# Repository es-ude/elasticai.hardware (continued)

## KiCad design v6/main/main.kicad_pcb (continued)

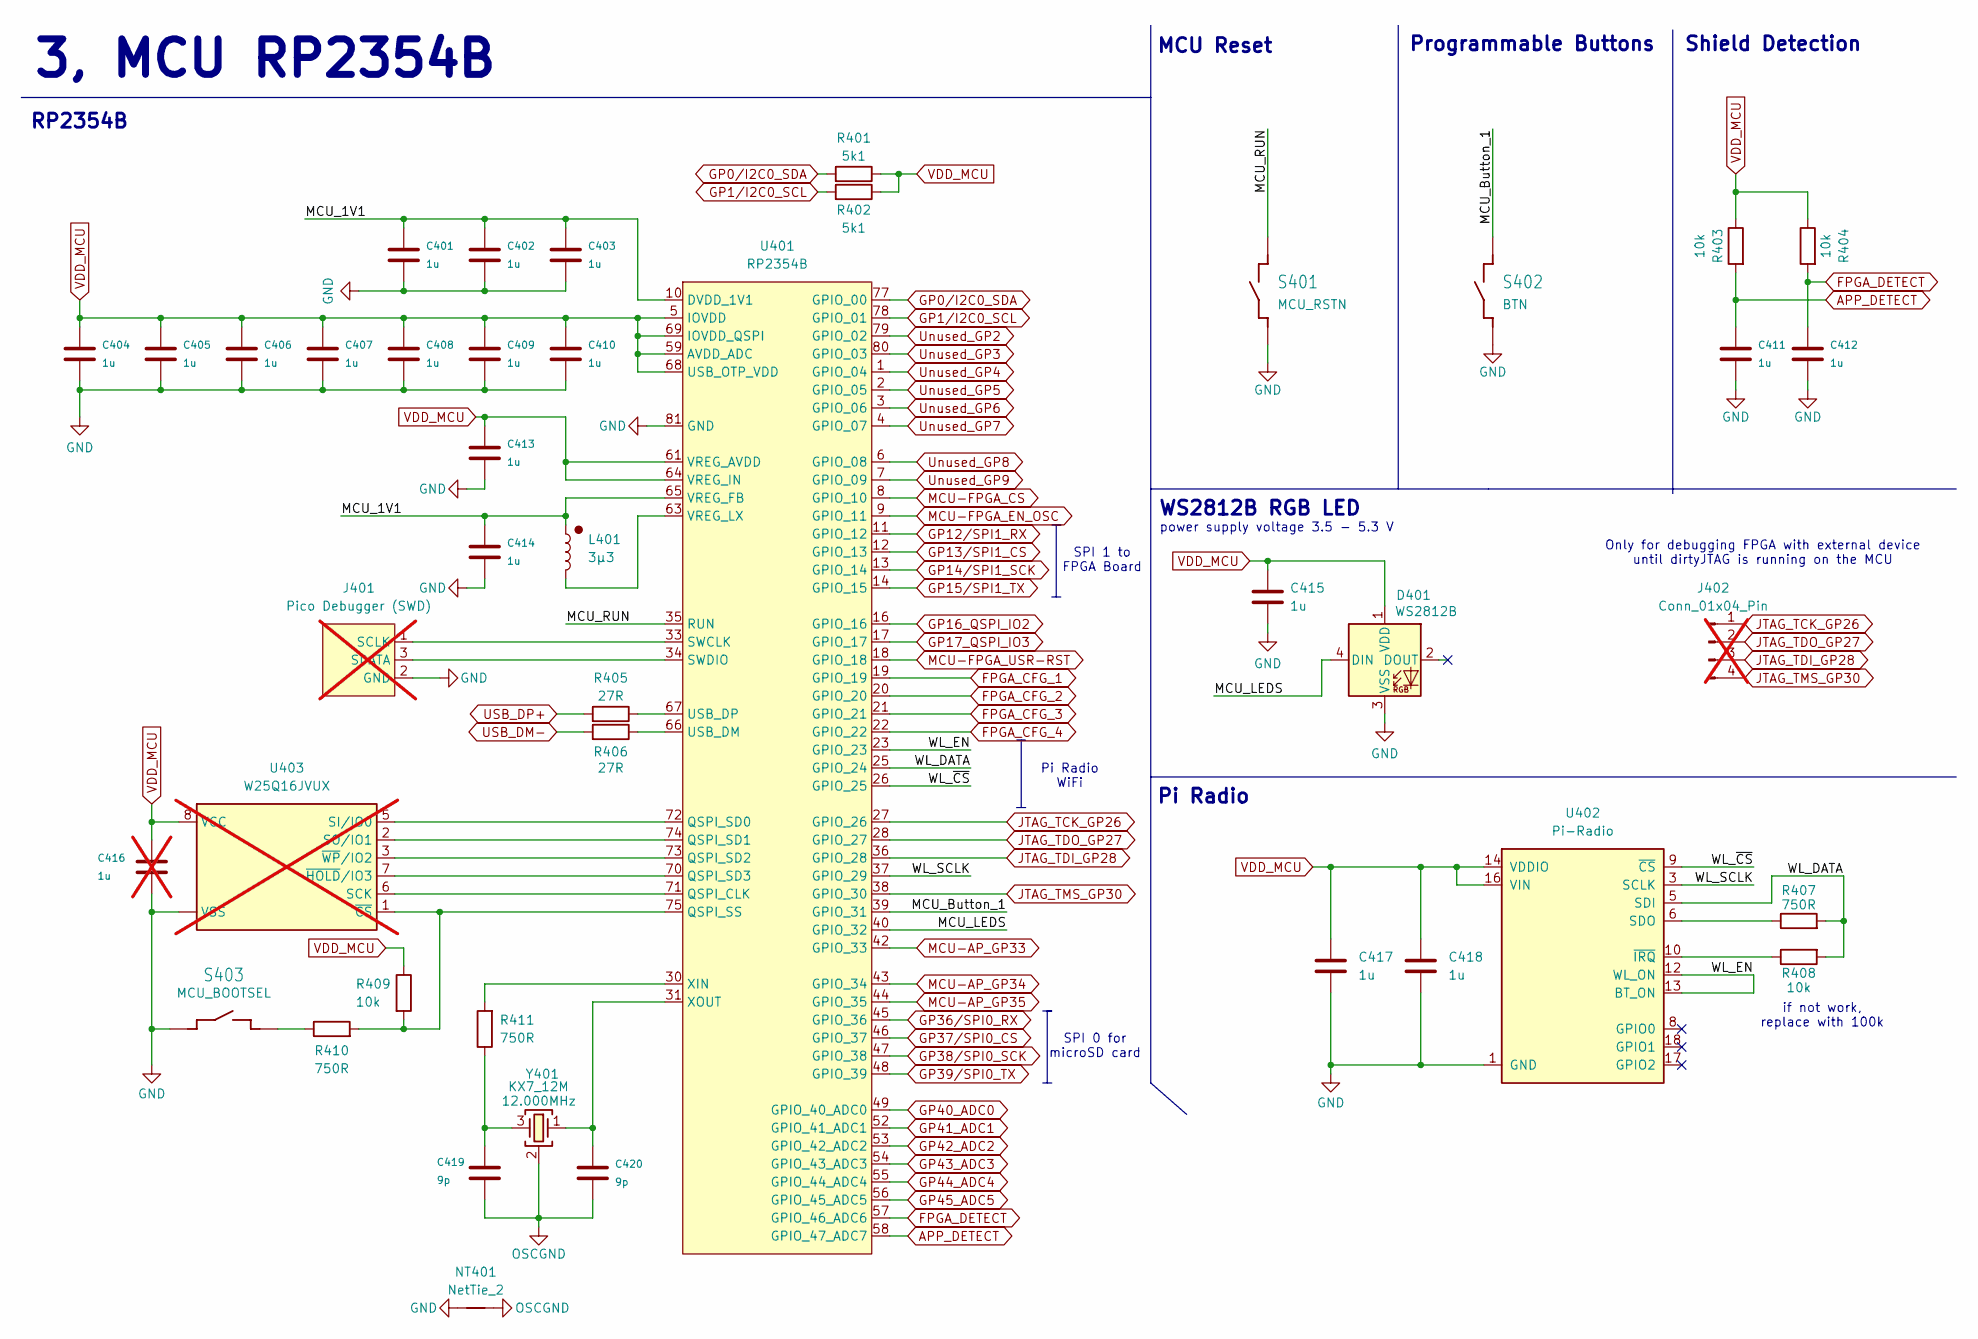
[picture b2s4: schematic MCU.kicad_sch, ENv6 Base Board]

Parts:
C401, C402, C403, C404, C405, C406, C407, C408, C409, C410, C411, C412, C413, C414, C415, C417, C418: 1u; C_0402_1005Metric
C416: 1u; C_0402_1005Metric; not fitted
C419, C420: 9p; C_0402_1005Metric
D401: WS2812B; LED_WS2812B_PLCC4_5.0x5.0mm_P3.2mm
J401: Pico Debugger (SWD); PinHeader_1x03_P2.00mm_Vertical; not fitted
J402: Conn_01x04_Pin; PinSocket_1x04_P2.00mm_Vertical; not fitted
L401: 3µ3; L_0805_2012_metric_Alligned_HandSolder; MPN AOTA-B201610S3R3-101-T
NT401: NetTie_2; NetTie-2_SMD_Pad0.5mm
R401, R402: 5k1; R_0402_1005Metric
R403, R404, R408, R409: 10k; R_0402_1005Metric
R405, R406: 27R; R_0402_1005Metric
R407, R410, R411: 750R; R_0402_1005Metric
S401: MCU_RSTN; TACTILE-SWITCH; MPN 612-TL3365AF180QG
S402: BTN; TACTILE-SWITCH; MPN 612-TL3365AF180QG
S403: MCU_BOOTSEL; TACTILE-SWITCH; MPN 612-TL3365AF180QG
U401: RP2354B; QFN-80_EP_10x10_Pitch0.4mm
U402: Pi-Radio; RPi-Radio-Module
U403: W25Q16JVUX; USON-8-1EP_3x2mm_P0.5mm_EP0.2x1.6mm; not fitted
Y401: KX7_12M; KX-7; MPN ABM8G-25.000MHZ-18-D2Y-T3

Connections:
/MCU/MCU_1V1: C401.2, C402.2, C403.2, C414.2, L401.1, U401.10 (DVDD_1V1), U401.32 (DVDD_1V1), U401.51 (DVDD_1V1), U401.65 (VREG_FB)
/MCU/MCU_Button_1: S402.3 (2), S402.4 (2), U401.39 (GPIO_31)
/MCU/MCU_LEDS: D401.4 (DIN), U401.40 (GPIO_32)
/MCU/MCU_RUN: S401.3 (2), S401.4 (2), U401.35 (RUN)
/MCU/WL_DATA: R407.2, R408.2, U401.25 (GPIO_24), U402.5 (SDI)
/MCU/WL_EN: U401.23 (GPIO_23), U402.12 (WL_ON), U402.13 (BT_ON)
/MCU/WL_SCLK: U401.37 (GPIO_29), U402.3 (SCLK)
/MCU/WL_~CS: U401.26 (GPIO_25), U402.9 (~CS)
APP_DETECT: C411.2, R403.2, U401.58 (GPIO_47_ADC7); also elsewhere on the board
FPGA_CFG_1: U401.19 (GPIO_19); also elsewhere on the board
FPGA_CFG_2: U401.20 (GPIO_20); also elsewhere on the board
FPGA_CFG_3: U401.21 (GPIO_21); also elsewhere on the board
FPGA_CFG_4: U401.22 (GPIO_22); also elsewhere on the board
FPGA_DETECT: C412.2, R404.2, U401.57 (GPIO_46_ADC6); also elsewhere on the board
GND: C401.1, C402.1, C403.1, C404.1, C405.1, C406.1, C407.1, C408.1, C409.1, C410.1, C411.1, C412.1, C413.1, C414.1, C415.2, C416.2, C417.2, C418.2, D401.3 (VSS), J401.2 (GND), NT401.1, S401.1, S401.2 (1), S402.1, S402.2 (1), S403.1, S403.2 (1), U401.62 (GND), U401.81 (GND), U402.1 (GND), U402.4 (GND), U402.7 (GND), U402.11 (GND), U402.15 (GND), U402.21 (GND), U403.4 (VSS), U403.9 (VSS); also elsewhere on the board
GP0/I2C0_SDA: R401.2, U401.77 (GPIO_00); also elsewhere on the board
GP1/I2C0_SCL: R402.2, U401.78 (GPIO_01); also elsewhere on the board
GP12/SPI1_RX: U401.11 (GPIO_12); also elsewhere on the board
GP13/SPI1_CS: U401.12 (GPIO_13); also elsewhere on the board
GP14/SPI1_SCK: U401.13 (GPIO_14); also elsewhere on the board
GP15/SPI1_TX: U401.14 (GPIO_15); also elsewhere on the board
GP16_QSPI_IO2: U401.16 (GPIO_16); also elsewhere on the board
GP17_QSPI_IO3: U401.17 (GPIO_17); also elsewhere on the board
GP36/SPI0_RX: U401.45 (GPIO_36); also elsewhere on the board
GP37/SPI0_CS: U401.46 (GPIO_37); also elsewhere on the board
GP38/SPI0_SCK: U401.47 (GPIO_38); also elsewhere on the board
GP39/SPI0_TX: U401.48 (GPIO_39); also elsewhere on the board
GP40_ADC0: U401.49 (GPIO_40_ADC0); also elsewhere on the board
GP41_ADC1: U401.52 (GPIO_41_ADC1); also elsewhere on the board
GP42_ADC2: U401.53 (GPIO_42_ADC2); also elsewhere on the board
GP43_ADC3: U401.54 (GPIO_43_ADC3); also elsewhere on the board
GP44_ADC4: U401.55 (GPIO_44_ADC4); also elsewhere on the board
GP45_ADC5: U401.56 (GPIO_45_ADC5); also elsewhere on the board
JTAG_TCK_GP26: J402.1, U401.27 (GPIO_26); also elsewhere on the board
JTAG_TDI_GP28: J402.3, U401.36 (GPIO_28); also elsewhere on the board
JTAG_TDO_GP27: J402.2, U401.28 (GPIO_27); also elsewhere on the board
JTAG_TMS_GP30: J402.4, U401.38 (GPIO_30); also elsewhere on the board
MCU-AP_GP33: U401.42 (GPIO_33); also elsewhere on the board
MCU-AP_GP34: U401.43 (GPIO_34); also elsewhere on the board
MCU-AP_GP35: U401.44 (GPIO_35); also elsewhere on the board
MCU-FPGA_CS: U401.8 (GPIO_10); also elsewhere on the board
MCU-FPGA_EN_OSC: U401.9 (GPIO_11); also elsewhere on the board
MCU-FPGA_USR-RST: U401.18 (GPIO_18); also elsewhere on the board
unnamed: C419.2, R411.1, Y401.3
unnamed: J401.1 (SCLK), U401.33 (SWCLK)
unnamed: J401.3 (SDATA), U401.34 (SWDIO)
unnamed: R410.1, S403.3 (2), S403.4 (2)
unnamed: U401.71 (QSPI_CLK), U403.6 (SCK)
unnamed: U401.72 (QSPI_SD0), U403.5 (SI/IO0)
unnamed: U401.74 (QSPI_SD1), U403.2 (SO/IO1)
unnamed: U401.73 (QSPI_SD2), U403.3 (~WP/IO2)
unnamed: U401.70 (QSPI_SD3), U403.7 (~HOLD/IO3)
unnamed: R409.2, R410.2, U401.75 (QSPI_SS), U403.1 (~CS)
unnamed: R406.1, U401.66 (USB_DM)
unnamed: R405.1, U401.67 (USB_DP)
unnamed: L401.2, U401.63 (VREG_LX)
unnamed: R411.2, U401.30 (XIN)
unnamed: C420.2, U401.31 (XOUT), Y401.1
unnamed: R407.1, U402.6 (SDO)
unnamed: R408.1, U402.10 (~IRQ)
OSCGND: C419.1, C420.1, NT401.2, Y401.2 (SH), Y401.4 (SH)
USB_DM-: R406.2; also elsewhere on the board
USB_DP+: R405.2; also elsewhere on the board
Unused_GP2: U401.79 (GPIO_02); also elsewhere on the board
Unused_GP3: U401.80 (GPIO_03); also elsewhere on the board
Unused_GP4: U401.1 (GPIO_04); also elsewhere on the board
Unused_GP5: U401.2 (GPIO_05); also elsewhere on the board
Unused_GP6: U401.3 (GPIO_06); also elsewhere on the board
Unused_GP7: U401.4 (GPIO_07); also elsewhere on the board
Unused_GP8: U401.6 (GPIO_08); also elsewhere on the board
Unused_GP9: U401.7 (GPIO_09); also elsewhere on the board
VDD_MCU: C404.2, C405.2, C406.2, C407.2, C408.2, C409.2, C410.2, C413.2, C415.1, C416.1, C417.1, C418.1, D401.1 (VDD), R401.1, R402.1, R403.1, R404.1, R409.1, U401.5 (IOVDD), U401.15 (IOVDD), U401.24 (IOVDD), U401.29 (IOVDD), U401.41 (IOVDD), U401.50 (IOVDD), U401.59 (AVDD_ADC), U401.60 (IOVDD), U401.61 (VREG_AVDD), U401.64 (VREG_IN), U401.68 (USB_OTP_VDD), U401.69 (IOVDD_QSPI), U401.76 (IOVDD), U402.14 (VDDIO), U402.16 (VIN), U403.8 (VCC); also elsewhere on the board

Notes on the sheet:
SPI 0 for microSD card
Programmable Buttons
Pi Radio WiFi
Only for debugging FPGA with external device until dirtyJTAG is running on the MCU
Pi Radio
if not work, replace with 100k
RP2354B
SPI 1 to FPGA Board
3, MCU RP2354B
power supply voltage 3.5 - 5.3 V
WS2812B RGB LED
Shield Detection
MCU Reset

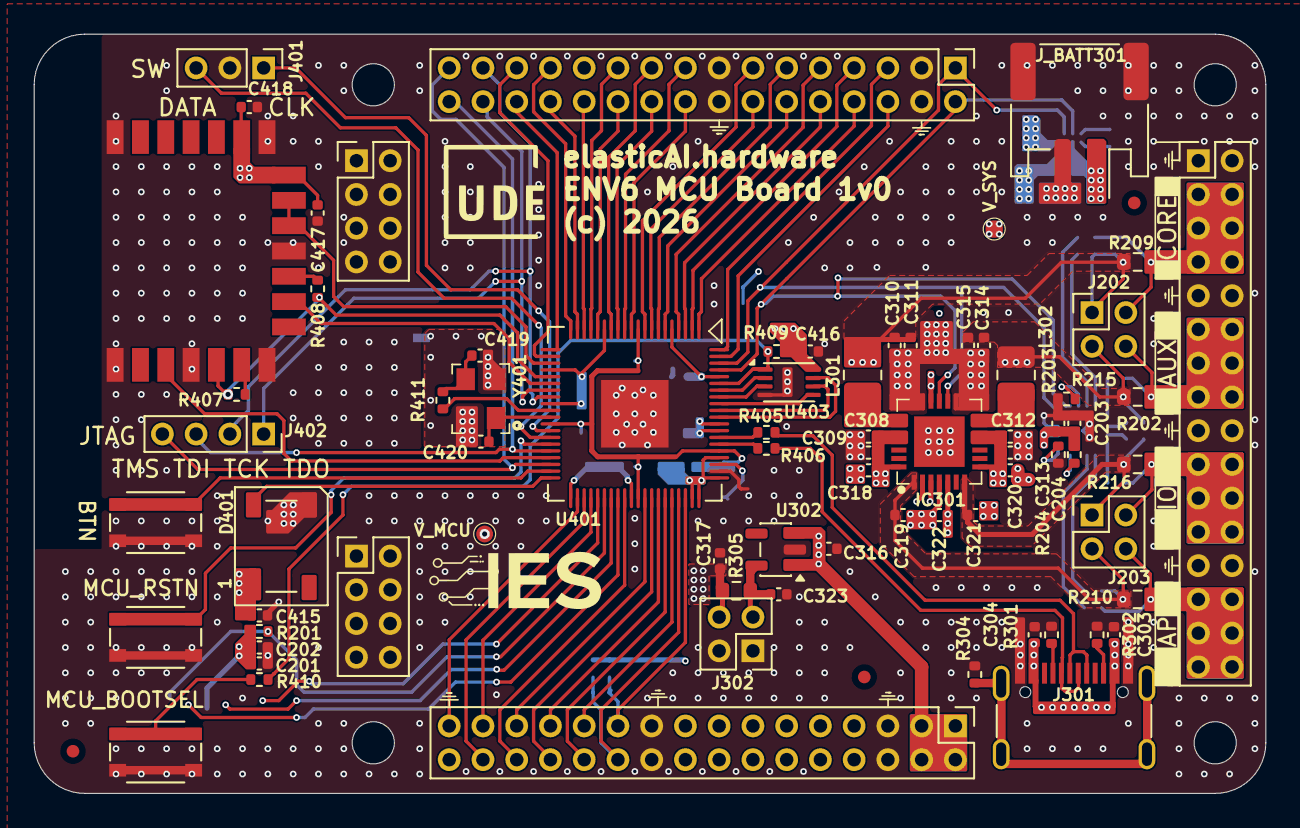
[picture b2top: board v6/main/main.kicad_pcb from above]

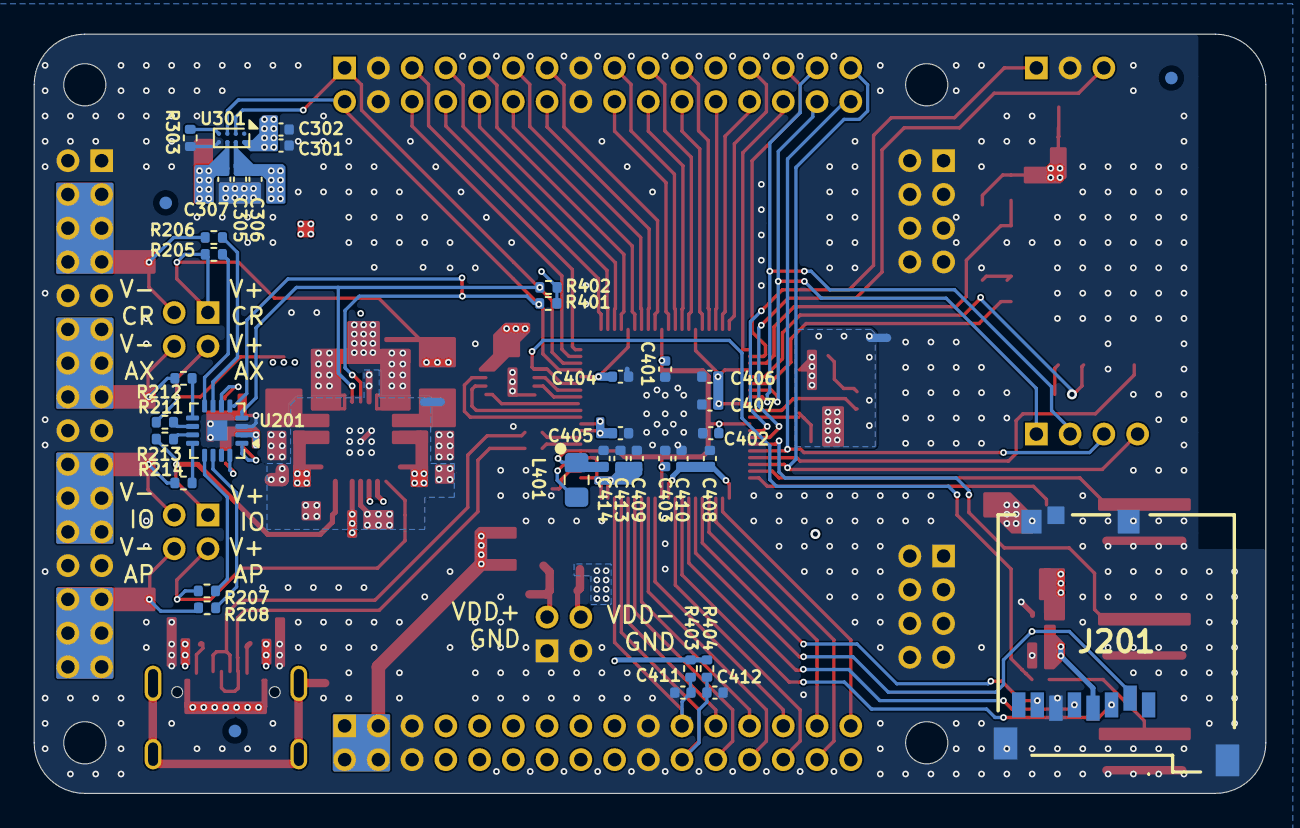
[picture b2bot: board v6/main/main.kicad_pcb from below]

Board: 4 copper layers, 73.0 x 45.0 mm, 113 parts (41 on the bottom side), 102 nets.

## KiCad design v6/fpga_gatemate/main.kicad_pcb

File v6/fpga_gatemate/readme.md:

# ENv6 FPGA Board: CologneChip GateMate M1A1/2

FPGA board (shield, rev 1.0) for the ENv6 base board with the CologneChip GateMate CCGM1A1 (schematic of the M1A1; the M1A2 is not designed yet). FPGA board ID: **2** (R1 + R2 + R3 = 750 Ω + 750 Ω + 27 Ω ≈ 1.5 kΩ to GND on `FPGA_DETECT`, see the [auto-identification](../readme.md#auto-identification-of-connected-boards)).

## Contents (KiCad sheets)

| Sheet         | Content                                                                                                          |
|---------------|------------------------------------------------------------------------------------------------------------------|
| `fpga_config` | IS25LP064D quad-SPI flash (U8), configuration mode pins `CFG_MD0 … 3`, pull-ups, SerDes header (J1, not fitted)  |
| `fpga_power`  | Supply decoupling, Si5351A clock generator (U7) with 25 MHz crystal (Y1), test points TP1/TP2                    |
| `fpga_io`     | IO banks of the FPGA, status LED (D1 with R4 = 750 Ω)                                                            |
| `translation` | Five TXB0108 level shifters (U1 … U5) between the FPGA (`VDD_IO`) and the connector (`VDDD_MCU`)                 |
| `connectors`  | ENv6 connector (base board and application board), ID resistors R1 … R3                                          |

### Configuration and clock

- **Mode pins:** `CFG_MD0 … 3` have 10 kΩ pull-downs fitted (R15 … R18); the pull-ups to `VDD_IO` (R11 … R14) are not fitted. The default setting is therefore `0000`. A different mode is selected by fitting a pull-up and removing the pull-down.
- **Flash:** The IS25LP064D (U8) is connected to the SPI configuration pins of the FPGA and, via level shifter U3, to the SPI1/QSPI lines of the MCU. Pull-ups (R20 … R24, 10 kΩ to `VDD_IO`) are on `CFG_DONE`, `CFG_FAILED_N`, flash CS and the flash IO2/IO3 lines.
- **Clock:** The Si5351A (U7) is controlled via I2C directly from the connector (A1, A2) and enabled via `EN_FPGA_OSC` (A13). `CLK0` drives the FPGA clock input `CLK0` (`FPGA_SYS_CLK`, test point TP1) through a 27 Ω series resistor; `CLK7` is available at test point TP2. Spread spectrum is disabled (`SSEN` pulled low by R10, R9 not fitted). The crystal load capacitors C41 and C45 (12 pF) are placed but not fitted; the internal load capacitance of the Si5351A is used.
- **SerDes:** The SerDes lines (`SER_CLK`, `SER_TX`, `SER_RX`) are only routed to the pin header J1, which is not fitted. R19 (750 Ω) is the SerDes termination resistor.

## Power Supply

| Rail   | Pins      | Net label | Use                                                                                             |
|--------|-----------|-----------|-------------------------------------------------------------------------------------------------|
| `PSU1` | C3 … C8   | `1V0`     | FPGA core, PLL and SerDes (`VDD_CORE`)                                                          |
| `PSU2` | C11 … C16 | `2V5`     | All IO banks (`VDD_IO`), flash, `VCCA` of the level shifters, Si5351A output supplies, pull-ups |

`VDD_PLL` (R27), `VDD_SER_PLL` (R26) and `VDD_SER` (R25) are fed from `1V0` through a 27 Ω series resistor each. On the FPGA side each of these three nodes has 3 × 1 µF, 10 µF and 100 nF to GND as an RC filter. Replace the resistors by 0 Ω if the voltage drop at the pins gets too large (the datasheet allows 0.95 … 1.05 V in economy mode).

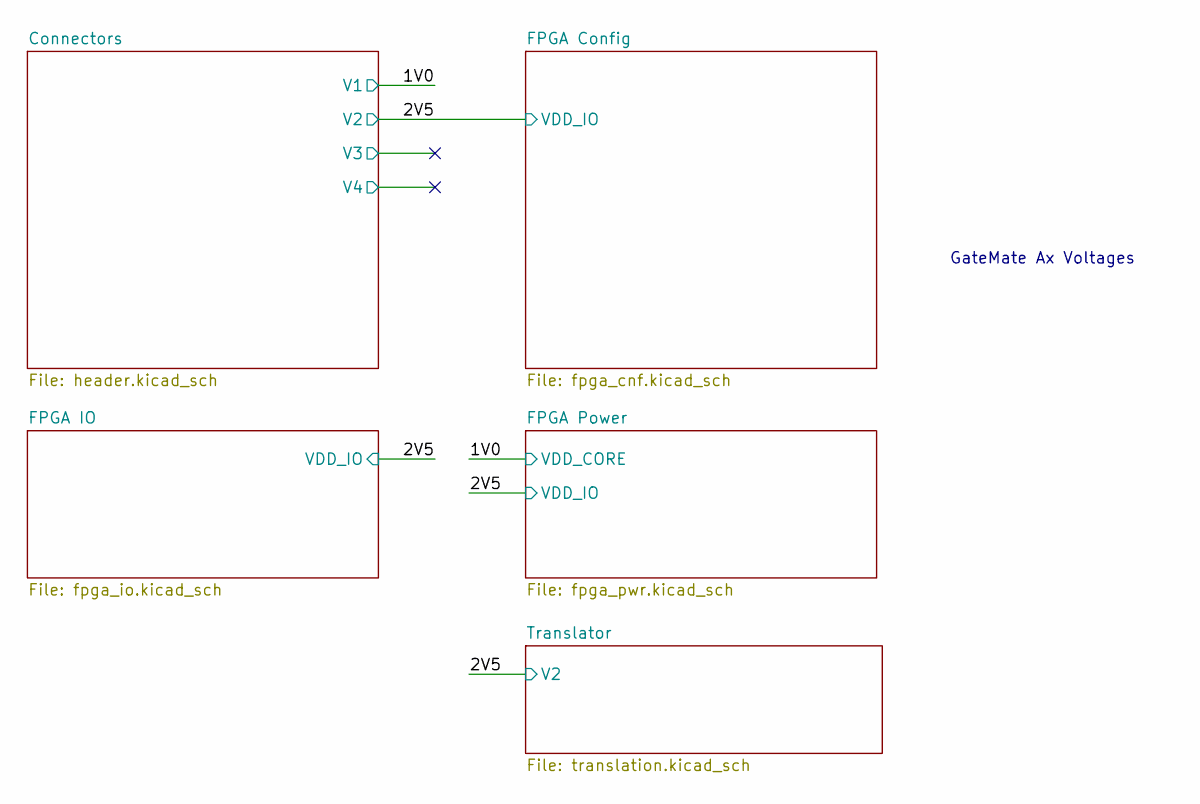
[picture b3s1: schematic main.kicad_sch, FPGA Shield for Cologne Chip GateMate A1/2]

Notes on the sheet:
GateMate Ax Voltages

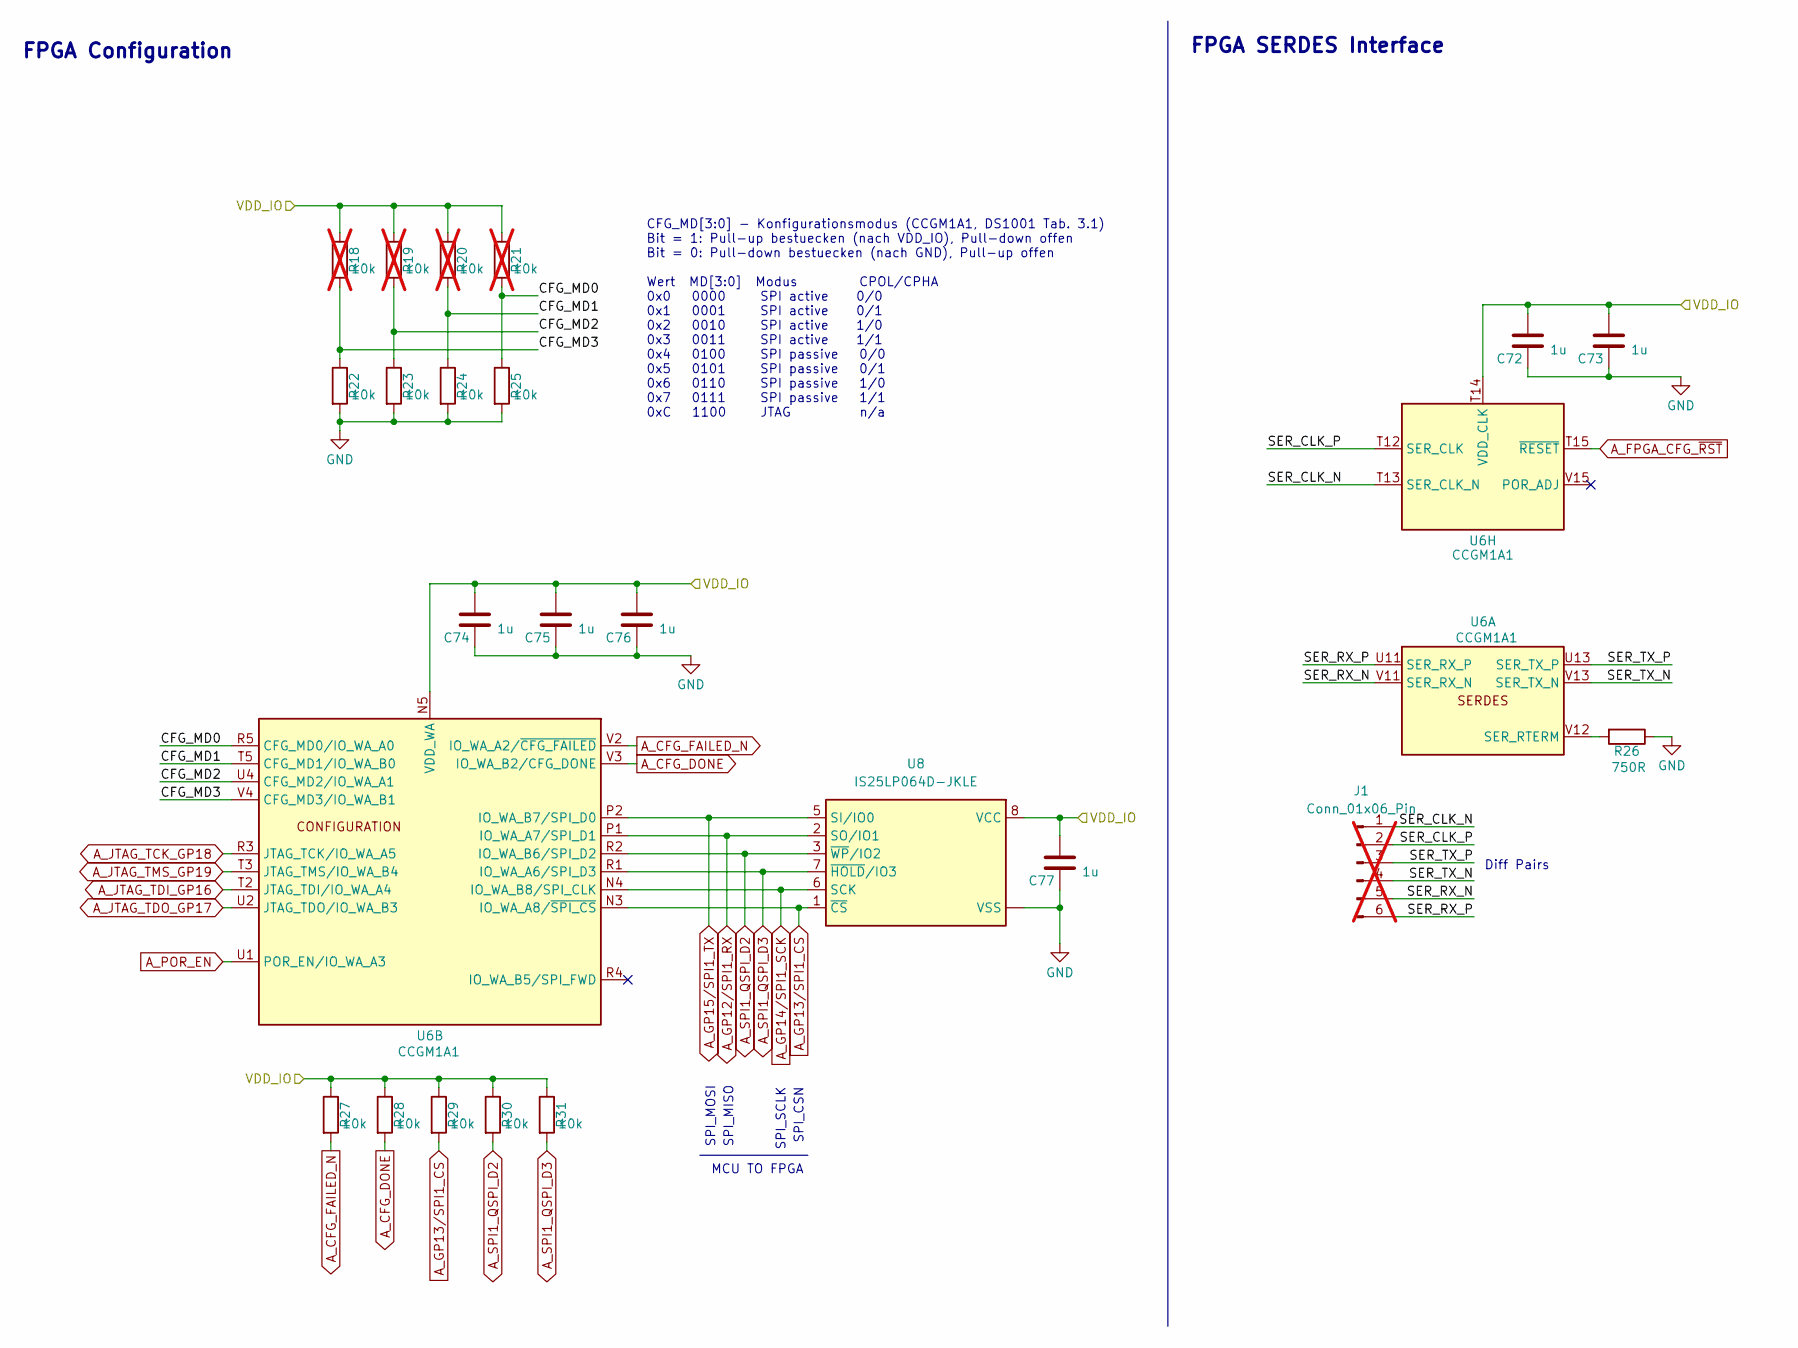
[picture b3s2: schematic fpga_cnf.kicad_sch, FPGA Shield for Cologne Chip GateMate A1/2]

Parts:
C72, C73, C74, C75, C76, C77: 1u; C_0402_1005Metric
J1: Conn_01x06_Pin; PinHeader_1x06_P2.54mm_Vertical; not fitted
R18, R19, R20, R21: 10k; R_0402_1005Metric; not fitted
R22, R23, R24, R25, R27, R28, R29, R30, R31: 10k; R_0402_1005Metric
R26: 750R; R_0402_1005Metric
U6: CCGM1A1; BGA-324_15.0x15.0mm_Layout18x18_P0.8mm_Ball0.5mm_Pad0.4mm_N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
U8: IS25LP064D-JKLE; WSON-8-1EP_6x5mm_P1.27mm_EP3.4x4.3mm

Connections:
/2V5: C72.2, C73.2, C74.2, C75.2, C76.2, C77.2, R18.1, R19.1, R20.1, R21.1, R27.1, R28.1, R29.1, R30.1, R31.1, U6.N5 (VDD_WA), U6.P3 (VDD_WA), U6.P5 (VDD_WA), U6.T1 (VDD_WA), U6.T14 (VDD_CLK), U6.U3 (VDD_WA), U8.8 (VCC); also elsewhere on the board
/FPGA Config/CFG_MD0: R21.2, R25.1, U6.R5 (CFG_MD0/IO_WA_A0)
/FPGA Config/CFG_MD1: R20.2, R24.1, U6.T5 (CFG_MD1/IO_WA_B0)
/FPGA Config/CFG_MD2: R19.2, R23.1, U6.U4 (CFG_MD2/IO_WA_A1)
/FPGA Config/CFG_MD3: R18.2, R22.1, U6.V4 (CFG_MD3/IO_WA_B1)
/FPGA Config/SER_CLK_N: J1.1, U6.T13 (SER_CLK_N)
/FPGA Config/SER_CLK_P: J1.2, U6.T12 (SER_CLK)
/FPGA Config/SER_RX_N: J1.5, U6.V11 (SER_RX_N)
/FPGA Config/SER_RX_P: J1.6, U6.U11 (SER_RX_P)
/FPGA Config/SER_TX_N: J1.4, U6.V13 (SER_TX_N)
/FPGA Config/SER_TX_P: J1.3, U6.U13 (SER_TX_P)
A_CFG_DONE: R28.2, U6.V3 (IO_WA_B2/CFG_DONE); also elsewhere on the board
A_CFG_FAILED_N: R27.2, U6.V2 (IO_WA_A2/~CFG_FAILED); also elsewhere on the board
A_FPGA_CFG_~RST: U6.T15 (~RESET); also elsewhere on the board
A_GP12/SPI1_RX: U6.P1 (IO_WA_A7/SPI_D1), U8.2 (SO/IO1); also elsewhere on the board
A_GP13/SPI1_CS: R29.2, U6.N3 (IO_WA_A8/~SPI_CS), U8.1 (~CS); also elsewhere on the board
A_GP14/SPI1_SCK: U6.N4 (IO_WA_B8/SPI_CLK), U8.6 (SCK); also elsewhere on the board
A_GP15/SPI1_TX: U6.P2 (IO_WA_B7/SPI_D0), U8.5 (SI/IO0); also elsewhere on the board
A_JTAG_TCK_GP18: U6.R3 (JTAG_TCK/IO_WA_A5); also elsewhere on the board
A_JTAG_TDI_GP16: U6.T2 (JTAG_TDI/IO_WA_A4); also elsewhere on the board
A_JTAG_TDO_GP17: U6.U2 (JTAG_TDO/IO_WA_B3); also elsewhere on the board
A_JTAG_TMS_GP19: U6.T3 (JTAG_TMS/IO_WA_B4); also elsewhere on the board
A_POR_EN: U6.U1 (POR_EN/IO_WA_A3); also elsewhere on the board
A_SPI1_QSPI_D2: R30.2, U6.R2 (IO_WA_B6/SPI_D2), U8.3 (~WP/IO2); also elsewhere on the board
A_SPI1_QSPI_D3: R31.2, U6.R1 (IO_WA_A6/SPI_D3), U8.7 (~HOLD/IO3); also elsewhere on the board
GND: C72.1, C73.1, C74.1, C75.1, C76.1, C77.1, R22.2, R23.2, R24.2, R25.2, R26.1, U8.4 (VSS), U8.9 (VSS); also elsewhere on the board
unnamed: R26.2, U6.V12 (SER_RTERM)

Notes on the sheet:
Diff Pairs
MCU TO FPGA
SPI_MOSI
SPI_MISO
CFG_MD[3:0] - Konfigurationsmodus (CCGM1A1, DS1001 Tab. 3.1) Bit = 1: Pull-up bestuecken (nach VDD_IO), Pull-down offen Bit = 0: Pull-down bestuecken (nach GND), Pull-up offen Wert MD[3:0] Modus CPOL/CPHA 0x0 0000 SPI active 0/0 0x1 0001 SPI active 0/1 0x2 0010 SPI active 1/0 0x3 0011 SPI active 1/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
FPGA Configuration
SPI_SCLK
FPGA SERDES Interface
SPI_CSN

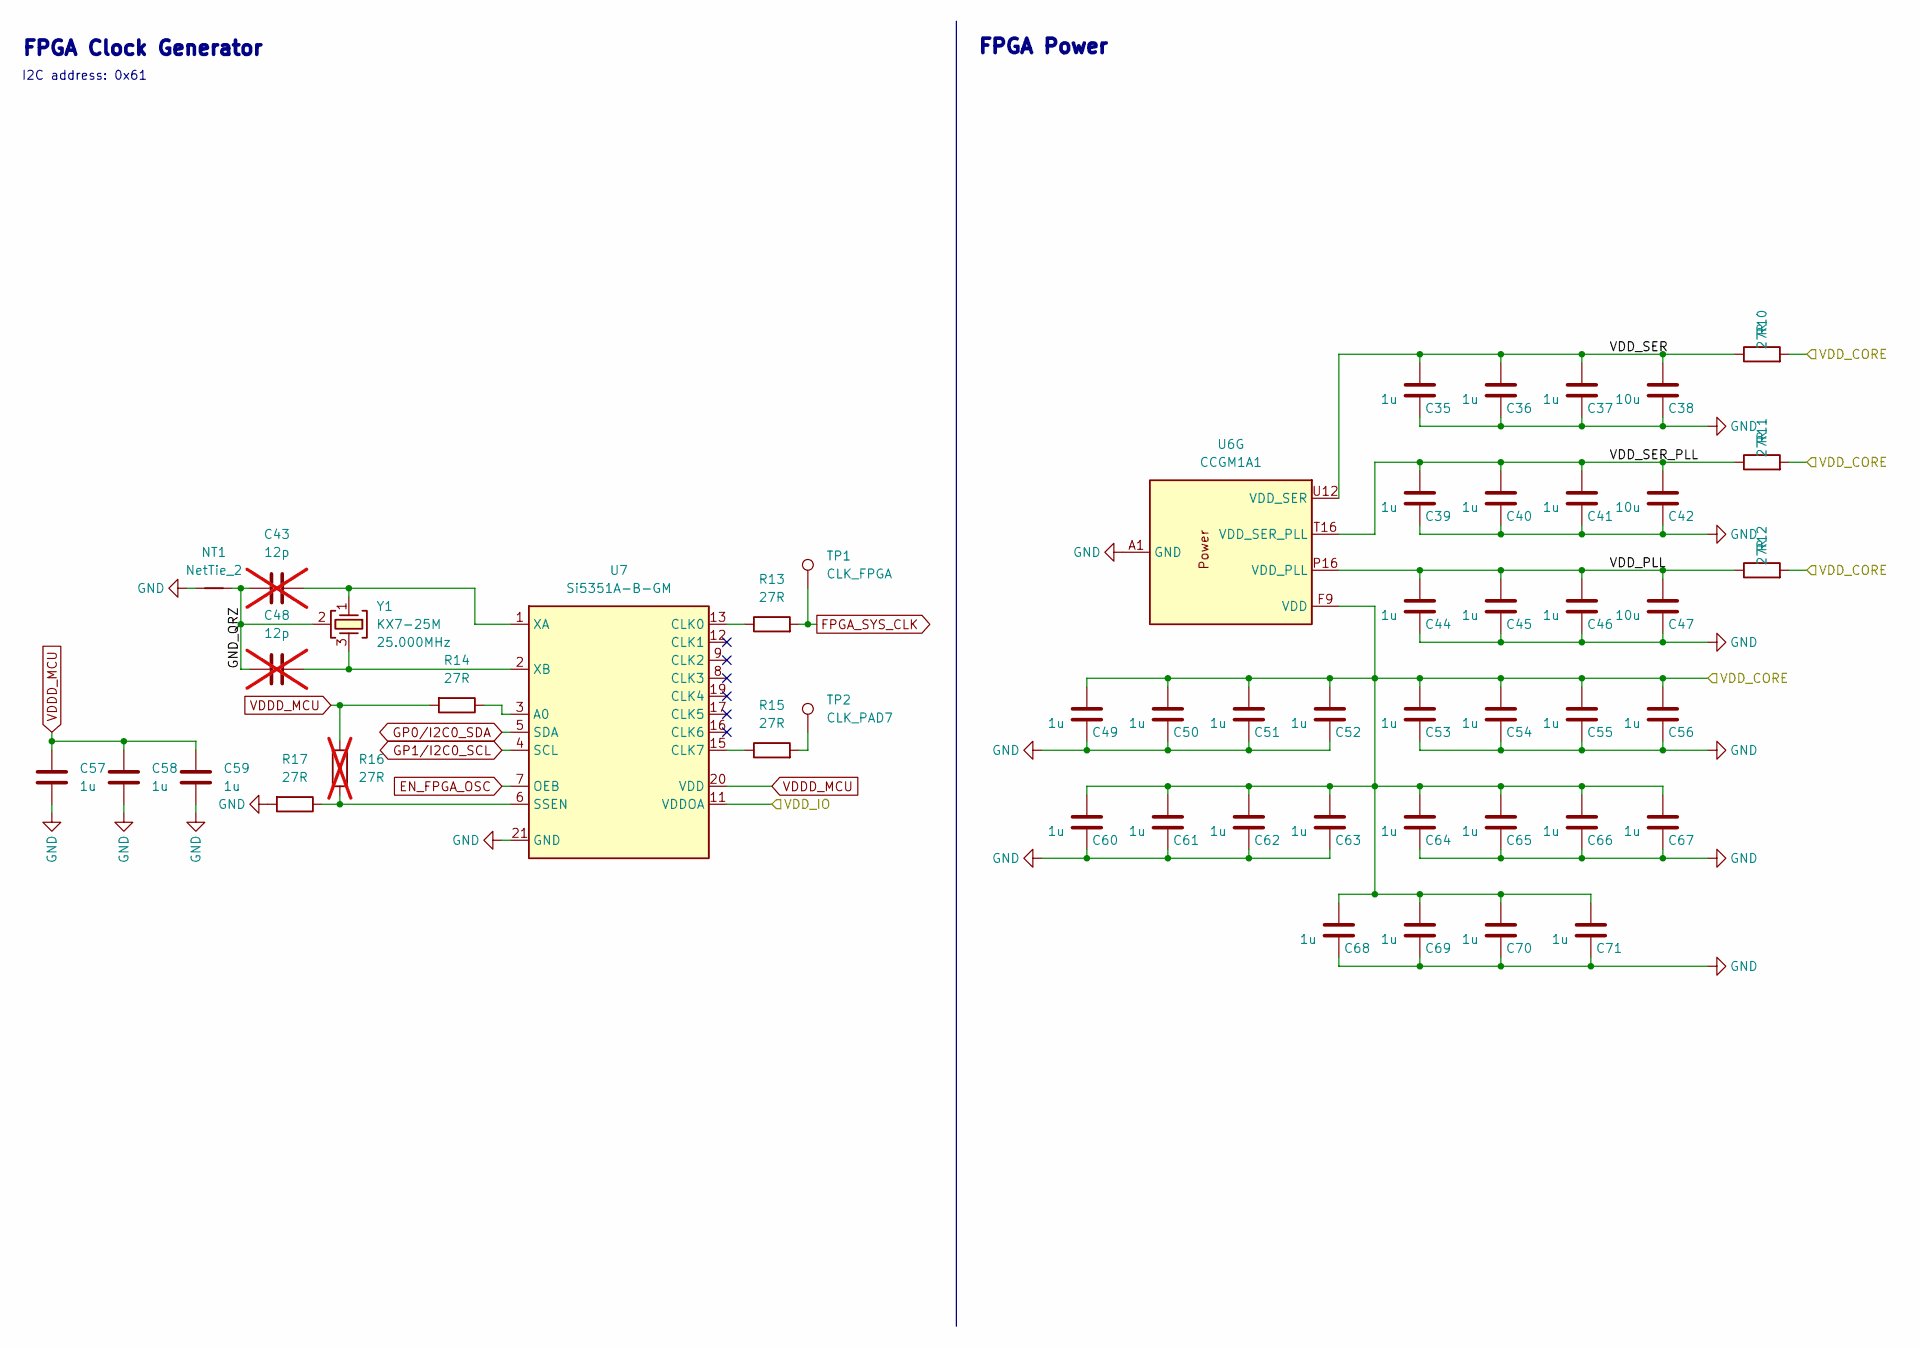
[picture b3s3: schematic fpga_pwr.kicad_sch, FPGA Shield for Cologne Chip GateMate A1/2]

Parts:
C35, C36, C37, C39, C40, C41, C44, C45, C46, C49, C50, C51, C52, C53, C54, C55, C56, C57, C58, C59, C60, C61, C62, C63, C64, C65, C66, C67, C68, C69, C70, C71: 1u; C_0402_1005Metric
C38, C42, C47: 10u; C_0402_1005Metric
C43, C48: 12p; C_0402_1005Metric; not fitted
NT1: NetTie_2; NetTie-2_SMD_Pad0.5mm
R10, R11, R12, R13, R14, R15, R17: 27R; R_0402_1005Metric
R16: 27R; R_0402_1005Metric; not fitted
TP1: CLK_FPGA; TestPoint_Pad_D1.0mm
TP2: CLK_PAD7; TestPoint_Pad_D1.0mm
U6: CCGM1A1; BGA-324_15.0x15.0mm_Layout18x18_P0.8mm_Ball0.5mm_Pad0.4mm_N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
U7: Si5351A-B-GM; QFN-20-1EP_4x4mm_P0.5mm_EP2.7x2.7mm
Y1: KX7-25M; KX-7; MPN ABM8G-25.000MHZ-18-D2Y-T3

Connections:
/1V0: C49.2, C50.2, C51.2, C52.2, C53.2, C54.2, C55.2, C56.2, C60.2, C61.2, C62.2, C63.2, C64.2, C65.2, C66.2, C67.2, C68.2, C69.2, C70.2, C71.2, R10.2, R11.2, R12.2, U6.F9 (VDD), U6.G6 (VDD), U6.G8 (VDD), U6.G10 (VDD), U6.G12 (VDD), U6.H7 (VDD), U6.H9 (VDD), U6.H11 (VDD), U6.H13 (VDD), U6.J6 (VDD), U6.J8 (VDD), U6.J10 (VDD), U6.J12 (VDD), U6.K7 (VDD), U6.K9 (VDD), U6.K11 (VDD), U6.K13 (VDD), U6.L6 (VDD), U6.L8 (VDD), U6.L10 (VDD), U6.L12 (VDD), U6.M7 (VDD), U6.M9 (VDD), U6.M11 (VDD), U6.M13 (VDD), U6.N6 (VDD), U6.N8 (VDD), U6.N10 (VDD); also elsewhere on the board
/2V5: U7.10 (VDDOB), U7.11 (VDDOA), U7.14 (VDDOD), U7.18 (VDDOC); also elsewhere on the board
/FPGA Power/GND_QRZ: C43.2, C48.2, NT1.2, Y1.2 (SH), Y1.4 (SH)
/FPGA Power/VDD_PLL: C44.2, C45.2, C46.2, C47.2, R12.1, U6.P16 (VDD_PLL)
/FPGA Power/VDD_SER: C35.2, C36.2, C37.2, C38.2, R10.1, U6.U12 (VDD_SER), U6.V17 (VDD_SER)
/FPGA Power/VDD_SER_PLL: C39.2, C40.2, C41.2, C42.2, R11.1, U6.T16 (VDD_SER_PLL)
EN_FPGA_OSC: U7.7 (OEB); also elsewhere on the board
FPGA_SYS_CLK: R13.2, TP1.1 (1_1); also elsewhere on the board
GND: C35.1, C36.1, C37.1, C38.1, C39.1, C40.1, C41.1, C42.1, C44.1, C45.1, C46.1, C47.1, C49.1, C50.1, C51.1, C52.1, C53.1, C54.1, C55.1, C56.1, C57.2, C58.2, C59.2, C60.1, C61.1, C62.1, C63.1, C64.1, C65.1, C66.1, C67.1, C68.1, C69.1, C70.1, C71.1, NT1.1, R17.2, U6.A1 (GND), U6.A7 (GND), U6.A10 (GND), U6.A13 (GND), U6.A18 (GND), U6.B16 (GND), U6.C1 (GND), U6.E5 (GND), U6.E7 (GND), U6.E9 (GND), U6.E11 (GND), U6.E13 (GND), U6.E18 (GND), U6.F1 (GND), U6.F6 (GND), U6.F8 (GND), U6.F10 (GND), U6.F12 (GND), U6.F14 (GND), U6.G5 (GND), U6.G7 (GND), U6.G9 (GND), U6.G11 (GND), U6.G13 (GND), U6.H6 (GND), U6.H8 (GND), U6.H10 (GND), U6.H12 (GND), U6.H14 (GND), U6.H18 (GND), U6.J1 (GND), U6.J5 (GND), U6.J7 (GND), U6.J9 (GND), U6.J11 (GND), U6.J13 (GND), U6.K6 (GND), U6.K8 (GND), U6.K10 (GND), U6.K12 (GND), U6.K14 (GND), U6.L5 (GND), U6.L7 (GND), U6.L9 (GND), U6.L11 (GND), U6.L13 (GND), U6.L18 (GND), U6.M1 (GND), U6.M6 (GND), U6.M8 (GND), U6.M10 (GND), U6.M12 (GND), U6.M16 (GND), U6.N7 (GND), U6.N9 (GND), U6.N12 (GND), U6.N17 (GND), U6.P4 (GND), U6.P7 (GND), U6.P9 (GND), U6.R12 (GND), U6.R16 (GND), U6.T4 (GND), U6.T11 (GND), U6.T17 (GND), U6.U14 (GND), U6.U15 (GND), U6.U16 (GND), U6.V1 (GND), U6.V6 (GND), U6.V9 (GND), U6.V14 (GND), U6.V16 (GND), U6.V18 (GND), U7.21 (GND); also elsewhere on the board
GP0/I2C0_SDA: U7.5 (SDA); also elsewhere on the board
GP1/I2C0_SCL: U7.4 (SCL); also elsewhere on the board
unnamed: R15.2, TP2.1 (1_1)
unnamed: R14.1, U7.3 (A0)
unnamed: R13.1, U7.13 (CLK0)
unnamed: R15.1, U7.15 (CLK7)
unnamed: R16.1, R17.1, U7.6 (SSEN)
unnamed: C43.1, U7.1 (XA), Y1.1
unnamed: C48.1, U7.2 (XB), Y1.3
VDDD_MCU: C57.1, C58.1, C59.1, R14.2, R16.2, U7.20 (VDD); also elsewhere on the board

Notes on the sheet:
FPGA Power
I2C address: 0x61
FPGA Clock Generator
